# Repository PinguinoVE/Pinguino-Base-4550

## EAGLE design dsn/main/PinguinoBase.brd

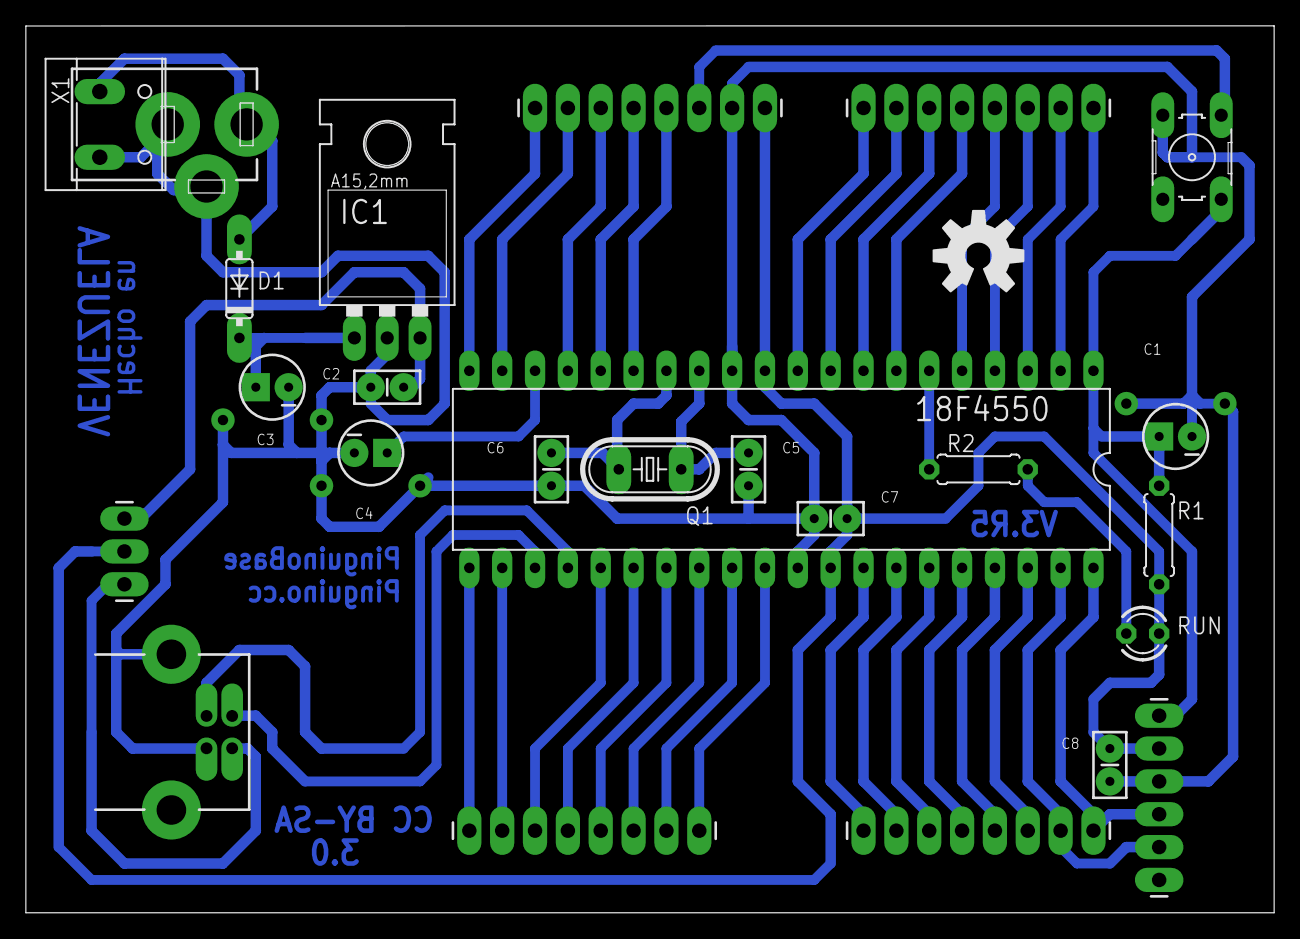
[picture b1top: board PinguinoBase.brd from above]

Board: 2 copper layers, 96.5 x 68.6 mm, 27 parts (0 on the bottom side), 43 nets.

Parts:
18F4550: DIL40
C1: 10uf/50v; CPOL-RADIAL-10UF-25V
C2, C7, C8: 0.1uf; CAP-PTH-SMALL2
C3: 0.33uf/50v; CPOL-RADIAL-10UF-25V
C4: 0.22uf/50v; CPOL-RADIAL-10UF-25V
C5, C6: 22pf; CAP-PTH-SMALL2
CC_TEXT1: CREATIVE_COMMONS
D1: 4007; DO35-7
DC-IN: DCJ0303
IC1: 7805; 78XXL
ICSP: 1X06_LONGPADS
JP1, JP2, JP4, JP5: 1X08_LONGPADS
JP3: 1X03_LONGPADS
LOGO1: OSHW-LOGOL; OSHW-LOGO-L
Q1: 20MHz; HC49U-V
R1: 10k; 0207/7
R2: 470; 0207/7
RESET: B3F-10XX
RUN: green; LED3MM
USB: USB-B-PTH
X1: W237-132

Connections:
+5V: 18F4550.11, 18F4550.32, C7.1, C8.1, ICSP.2, JP3.2, JP5.1, R1.2, RUN.A
D+: 18F4550.24, USB.D+
D-: 18F4550.23, USB.D-
GND: 18F4550.12, 18F4550.31, C1.2, C2.2, C3.2, C4.2, C5.2, C6.2, C7.2, C8.2, DC-IN.2, DC-IN.3, IC1.GND, ICSP.3, JP5.2, RESET.2, USB.GND, USB.S2, X1.2
unnamed: 18F4550.13, C5.1, Q1.1
unnamed: C3.1, D1.C, IC1.IN
unnamed: C2.1, IC1.OUT, JP3.3
unnamed: JP3.1, USB.VBUS
unnamed: 18F4550.14, C6.1, Q1.2
unnamed: 18F4550.18, C4.1
unnamed: R2.2, RUN.K
unnamed: 18F4550.6, R2.1
unnamed: D1.A, DC-IN.1, X1.1
PIN0: 18F4550.33, JP1.1
PIN1: 18F4550.34, JP1.2
PIN2: 18F4550.35, JP1.3
PIN3: 18F4550.36, JP1.4
PIN4: 18F4550.37, JP1.5
PIN5: 18F4550.38, JP1.6
PIN6: 18F4550.39, ICSP.5, JP1.7
PIN7: 18F4550.40, ICSP.4, JP1.8
PIN8: 18F4550.25, JP2.3
PIN9: 18F4550.26, JP2.4
PIN10: 18F4550.15, JP5.4
PIN11: 18F4550.16, JP5.5
PIN12: 18F4550.17, JP5.6
PIN13: 18F4550.2, JP4.1
PIN14: 18F4550.3, JP4.2
PIN15: 18F4550.4, JP4.3
PIN16: 18F4550.5, JP4.4
PIN17: 18F4550.7, JP4.5
PIN18: 18F4550.8, JP4.6
PIN19: 18F4550.9, JP4.7
PIN20: 18F4550.10, JP4.8
PIN21: 18F4550.19, JP5.7
PIN22: 18F4550.20, JP5.8
PIN23: 18F4550.21, JP2.1
PIN24: 18F4550.22, JP2.2
PIN25: 18F4550.27, JP2.5
PIN26: 18F4550.28, JP2.6
PIN27: 18F4550.29, JP2.7
PIN28: 18F4550.30, JP2.8
RESET: 18F4550.1, C1.1, ICSP.1, JP5.3, R1.1, RESET.3, RESET.4

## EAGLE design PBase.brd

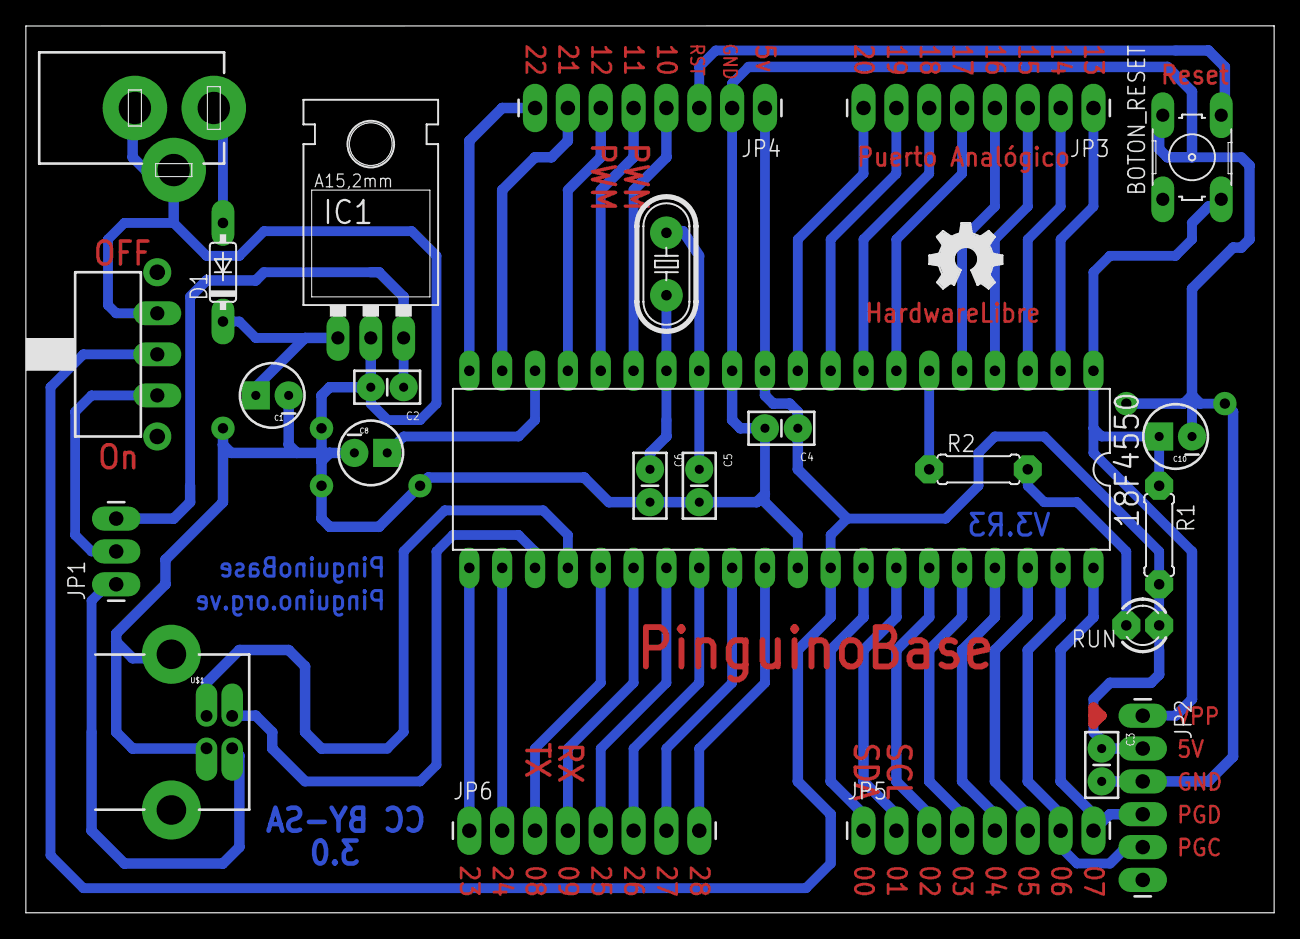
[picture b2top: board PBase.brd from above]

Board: 2 copper layers, 96.5 x 68.6 mm, 26 parts (0 on the bottom side), 44 nets.

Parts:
18F4550: DIL40
BOTON_RESET: B3F-10XX
C1: 0.33uf/50v; CPOL-RADIAL-10UF-25V
C2, C3, C4: 0.1uf; CAP-PTH-SMALL2
C5, C6: 22pf; CAP-PTH-SMALL2
C8: 0.22uf/50v; CPOL-RADIAL-10UF-25V
C10: 10uf/50v; CPOL-RADIAL-10UF-25V
D1: 4007; DO35-7
ENTRADA_DC: DCJ0303
IC1: 7805; 78XXL
JP1: 1X03_LONGPADS
JP2: 1X06_LONGPADS
JP3, JP4, JP5, JP6: 1X08_LONGPADS
LOGO1: OSHW_LOGO_FILLX0200-NT; OSHW_FILLX200_NOTEXT
Q1: 20MHz; HC49U-V
R1: 10k; 0207/7
R2: 470; 0207/7
RUN: LED3MM
S1: TL3XYO
U$1: USB+SHIELD; USB-B-PTH

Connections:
+5V: 18F4550.11, 18F4550.32, C3.1, C4.1, JP2.2, JP4.1, R1.2, RUN.A, S1.2
D+: 18F4550.24, U$1.D+
D-: 18F4550.23, U$1.D-
GND: 18F4550.12, 18F4550.31, BOTON_RESET.2, C1.2, C2.2, C3.2, C4.2, C5.2, C6.2, C8.2, C10.2, ENTRADA_DC.2, ENTRADA_DC.3, IC1.GND, JP2.3, JP4.2, S1.3, U$1.GND, U$1.S2
unnamed: 18F4550.13, C5.1, Q1.1
unnamed: C1.1, D1.C, IC1.IN
unnamed: C2.1, IC1.OUT, JP1.3
unnamed: JP1.1, U$1.VBUS
unnamed: 18F4550.14, C6.1, Q1.2
unnamed: 18F4550.18, C8.1
unnamed: R2.2, RUN.K
unnamed: 18F4550.6, R2.1
unnamed: JP1.2, S1.1
unnamed: D1.A, ENTRADA_DC.1
PIN0: 18F4550.33, JP5.1
PIN1: 18F4550.34, JP5.2
PIN2: 18F4550.35, JP5.3
PIN3: 18F4550.36, JP5.4
PIN4: 18F4550.37, JP5.5
PIN5: 18F4550.38, JP5.6
PIN6: 18F4550.39, JP2.5, JP5.7
PIN7: 18F4550.40, JP2.4, JP5.8
PIN8: 18F4550.25, JP6.3
PIN9: 18F4550.26, JP6.4
PIN10: 18F4550.15, JP4.4
PIN11: 18F4550.16, JP4.5
PIN12: 18F4550.17, JP4.6
PIN13: 18F4550.2, JP3.1
PIN14: 18F4550.3, JP3.2
PIN15: 18F4550.4, JP3.3
PIN16: 18F4550.5, JP3.4
PIN17: 18F4550.7, JP3.5
PIN18: 18F4550.8, JP3.6
PIN19: 18F4550.9, JP3.7
PIN20: 18F4550.10, JP3.8
PIN21: 18F4550.19, JP4.7
PIN22: 18F4550.20, JP4.8
PIN23: 18F4550.21, JP6.1
PIN24: 18F4550.22, JP6.2
PIN25: 18F4550.27, JP6.5
PIN26: 18F4550.28, JP6.6
PIN27: 18F4550.29, JP6.7
PIN28: 18F4550.30, JP6.8
RESET: 18F4550.1, BOTON_RESET.3, BOTON_RESET.4, C10.1, JP2.1, JP4.3, R1.1

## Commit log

2012-03-12 Actualización Eagle 6
2012-04-30 Update 3v4
2012-04-30 Clean Up
2013-12-16 OpenSource Hardware Good Practice template
2013-12-16 Diseño
2014-01-23 Update R3.5
    Nueva versión de PinguinoBase, a su versión 3.5, algunas modificaciones
    de forma, reorganización de componentes, como el Cristal, capacitores,
    eliminado switch de encendido, reorganizado de pistas.
2014-01-27 Agregado Bootloaders
    Bootloaders
2014-01-27 Algunos cambios
    Cambios simples en el diseño
2014-02-08 some Fixes
2014-02-08 Renumeracion de Componentes, mejoras en el BOM, y correccion a detalles esteticos en el Board
2014-02-08 Limpieza de cosas innecesarias
2014-02-09 Modificado posicion del Cristal
2015-01-31 CleanUp
2015-04-20 Add license file via addalicense.com
2015-04-20 Update Licence
    Cambio de licencia de GPL a CC

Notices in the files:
dsn/main/PinguinoBase.brd:
CC BY-SA
parts and their libraries:
SparkFun-Aesthetics: Licensing: CC v3.0 Share-Alike You are welcome to use this library for commercial purposes.
SparkFun-Aesthetics: Released under the Creative Commons Attribution Share-Alike 3.0 License
SparkFun-Aesthetics: http://creativecommons.org/licenses/by-sa/3.0
